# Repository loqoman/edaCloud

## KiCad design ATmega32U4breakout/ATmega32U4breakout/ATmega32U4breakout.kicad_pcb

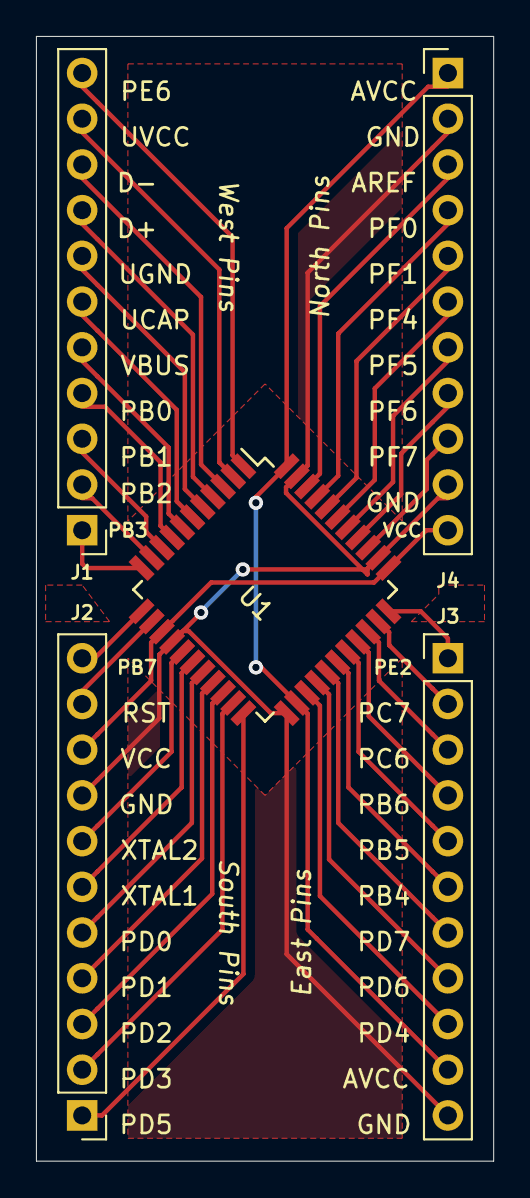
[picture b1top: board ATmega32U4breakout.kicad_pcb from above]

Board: 2 copper layers, 25.4 x 62.5 mm, 5 parts (0 on the bottom side), 39 nets.

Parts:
J1: West_Pin; PinHeader_1x11_P2.54mm_Vertical
J2: South_Pin; PinHeader_1x11_P2.54mm_Vertical
J3: East_Pin; PinHeader_1x11_P2.54mm_Vertical
J4: North_Pin; PinHeader_1x11_P2.54mm_Vertical
U1: ATmega32U4-AU; TQFP-44_10x10mm_P0.8mm

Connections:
AREF: J4.3, U1.42
AVCC: J3.10, J4.1, U1.24, U1.44
D+: J1.8, U1.4
D-: J1.9, U1.3
GND: J2.8, J3.11, J4.2, J4.10, U1.15, U1.23, U1.35, U1.43
PB0: J1.4, U1.8
PB1: J1.3, U1.9
PB2: J1.2, U1.10
PB3: J1.1, U1.11
PB4: J3.6, U1.28
PB5: J3.5, U1.29
PB6: J3.4, U1.30
PB7: J2.11, U1.12
PC6: J3.3, U1.31
PC7: J3.2, U1.32
PD0: J2.5, U1.18
PD1: J2.4, U1.19
PD2: J2.3, U1.20
PD3: J2.2, U1.21
PD4: J3.9, U1.25
PD5: J2.1, U1.22
PD6: J3.8, U1.26
PD7: J3.7, U1.27
PE2: J3.1, U1.33
PE6: J1.11, U1.1
PF0: J4.4, U1.41
PF1: J4.5, U1.40
PF4: J4.6, U1.39
PF5: J4.7, U1.38
PF6: J4.8, U1.37
PF7: J4.9, U1.36
RESET: J2.10, U1.13
UCAP: J1.6, U1.6
UGND: J1.7, U1.5
UVCC: J1.10, U1.2
VBUS: J1.5, U1.7
VCC: J2.9, J4.11, U1.14, U1.34
XTAL1: J2.6, U1.17
XTAL2: J2.7, U1.16

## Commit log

2019-05-21 :sparkles: 555 timer rev 1 (without lab notes)
2019-05-23 :recycle: Removing noise from schematic
2019-05-23 :sparkles: Beginning of Parallel series LED's project
2019-05-23 :bulb: Simple LED circuit for future reference
2019-05-28 File to test with simulator
2019-05-28 :fire: Cleaning up auto-created files for 555 timer
2019-05-28 :art: Updated Schematic for 555, now reflects most recent physical design
2019-08-13 :tada: Rev 1 commit of ATmega32 breakout board.
2020-07-24 :tada: Adding a project corresponding to chapter 2 + SPICE simulation learning
2020-07-25 :sparkles: some updates
2020-07-28 :White_check_mark: More simulator work, added a voltage divider + respective tags
